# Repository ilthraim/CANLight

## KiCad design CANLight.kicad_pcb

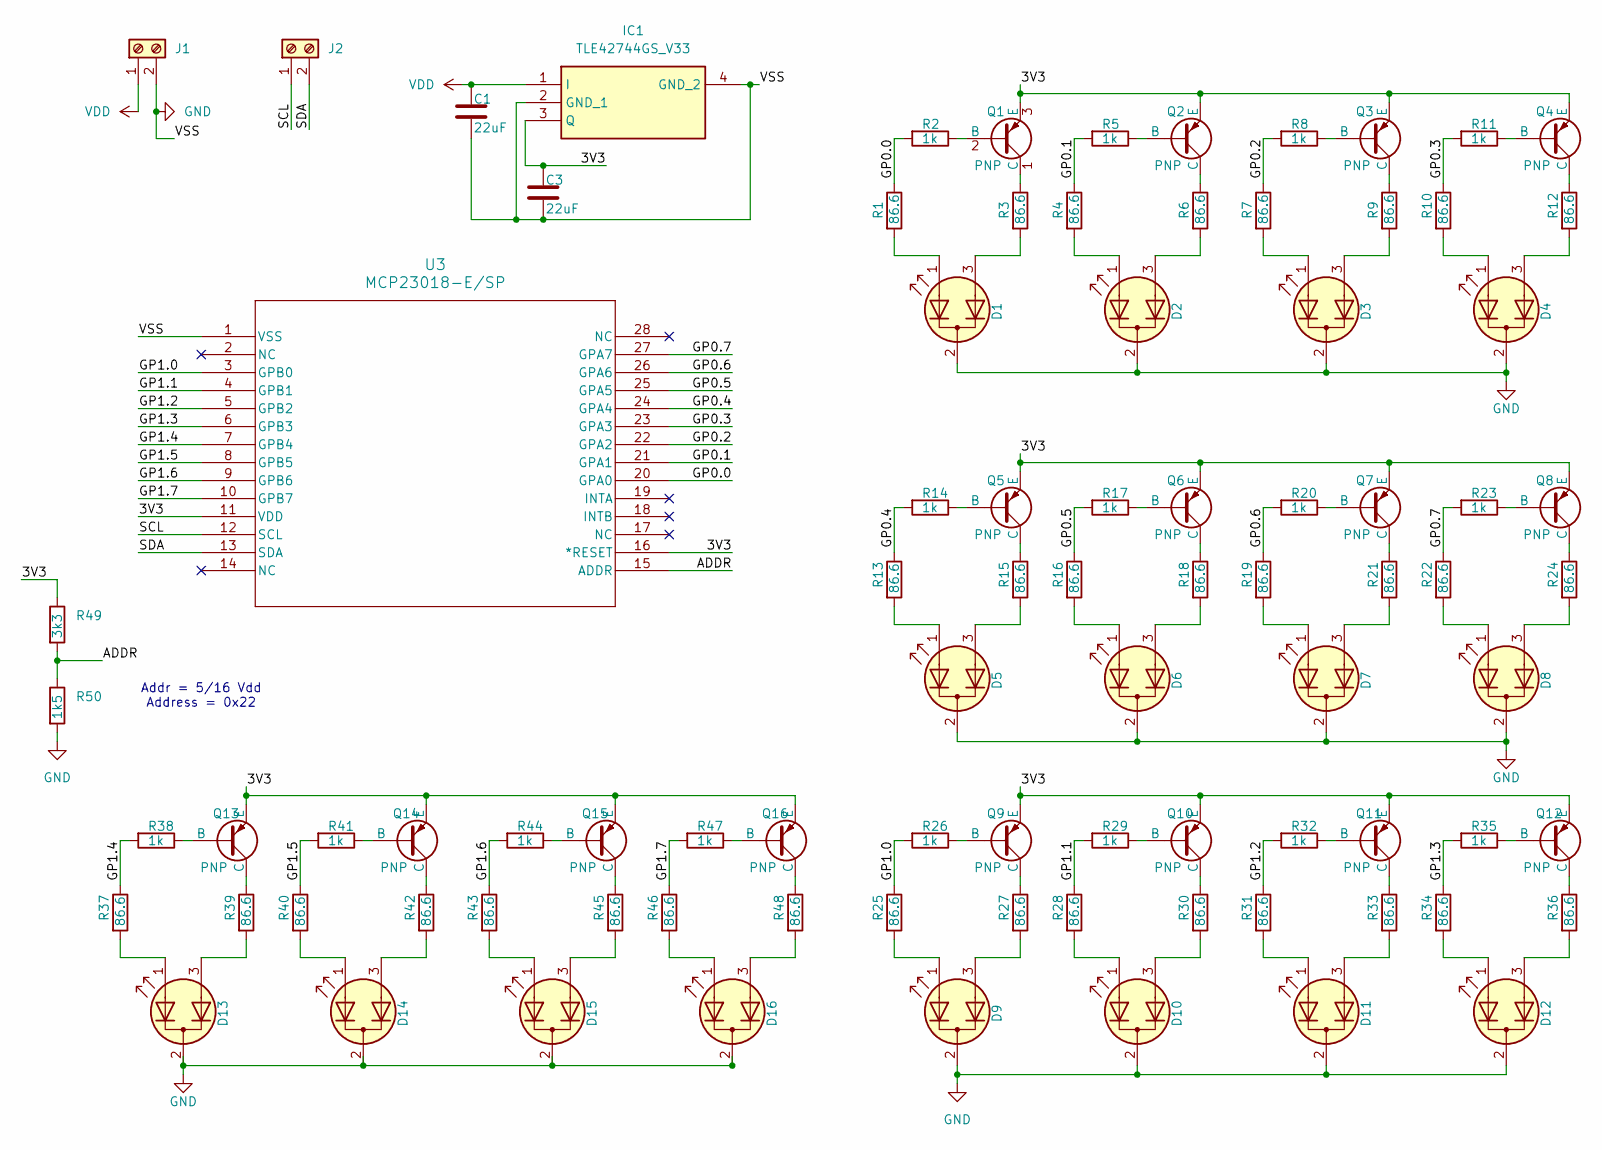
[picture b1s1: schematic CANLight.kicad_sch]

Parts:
C1, C3: 22uF; C_0805_2012Metric
D1, D2, D3, D4, D5, D6, D7, D8, D9, D10, D11, D12, D13, D14, D15, D16: LED_Dual_AKA; HLMP-40XX_BRA
IC1: TLE42744GS_V33; VREG_TLE42644GHTSA3; Mouser Part Number 726-TLE42744GSV33
J1, J2: Screw_Terminal_01x02; CONN_1935161_PXC
Q1, Q2, Q3, Q4, Q5, Q6, Q7, Q8, Q9, Q10, Q11, Q12, Q13, Q14, Q15, Q16: PNP; TO-92-3L_5P33X5P2_ONS
R1, R3, R4, R6, R7, R9, R10, R12, R13, R15, R16, R18, R19, R21, R22, R24, R25, R27, R28, R30, R31, R33, R34, R36, R37, R39, R40, R42, R43, R45, R46, R48: 86.6; R_0805_2012Metric
R2, R5, R8, R11, R14, R17, R20, R23, R26, R29, R32, R35, R38, R41, R44, R47: 1k; R_0805_2012Metric
R49: 3k3; R_0805_2012Metric
R50: 1k5; R_0805_2012Metric
U3: MCP23018-E/SP; SPDIP28_300MC_MCH

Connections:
/3V3: C3.1, IC1.3 (Q), Q1.3 (E), Q2.3 (E), Q3.3 (E), Q4.3 (E), Q5.3 (E), Q6.3 (E), Q7.3 (E), Q8.3 (E), Q9.3 (E), Q10.3 (E), Q11.3 (E), Q12.3 (E), Q13.3 (E), Q14.3 (E), Q15.3 (E), Q16.3 (E), R49.1, U3.11 (VDD), U3.16 (*RESET)
/ADDR: R49.2, R50.1, U3.15 (ADDR)
/GP0.0: R1.1, R2.2, U3.20 (GPA0)
/GP0.1: R4.1, R5.2, U3.21 (GPA1)
/GP0.2: R7.1, R8.2, U3.22 (GPA2)
/GP0.3: R10.1, R11.2, U3.23 (GPA3)
/GP0.4: R13.1, R14.2, U3.24 (GPA4)
/GP0.5: R16.1, R17.2, U3.25 (GPA5)
/GP0.6: R19.1, R20.2, U3.26 (GPA6)
/GP0.7: R22.1, R23.2, U3.27 (GPA7)
/GP1.0: R25.1, R26.2, U3.3 (GPB0)
/GP1.1: R28.1, R29.2, U3.4 (GPB1)
/GP1.2: R31.1, R32.2, U3.5 (GPB2)
/GP1.3: R34.1, R35.2, U3.6 (GPB3)
/GP1.4: R37.1, R38.2, U3.7 (GPB4)
/GP1.5: R40.1, R41.2, U3.8 (GPB5)
/GP1.6: R43.1, R44.2, U3.9 (GPB6)
/GP1.7: R46.1, R47.2, U3.10 (GPB7)
/SCL: J2.1, U3.12 (SCL)
/SDA: J2.2, U3.13 (SDA)
GND: C1.2, C3.2, D1.2 (K), D2.2 (K), D3.2 (K), D4.2 (K), D5.2 (K), D6.2 (K), D7.2 (K), D8.2 (K), D9.2 (K), D10.2 (K), D11.2 (K), D12.2 (K), D13.2 (K), D14.2 (K), D15.2 (K), D16.2 (K), IC1.2 (GND_1), IC1.4 (GND_2), J1.2, R50.2, U3.1 (VSS)
unnamed: D1.1 (A1), R1.2
unnamed: D1.3 (A2), R3.2
unnamed: D2.1 (A1), R4.2
unnamed: D2.3 (A2), R6.2
unnamed: D3.1 (A1), R7.2
unnamed: D3.3 (A2), R9.2
unnamed: D4.1 (A1), R10.2
unnamed: D4.3 (A2), R12.2
unnamed: D5.1 (A1), R13.2
unnamed: D5.3 (A2), R15.2
unnamed: D6.1 (A1), R16.2
unnamed: D6.3 (A2), R18.2
unnamed: D7.1 (A1), R19.2
unnamed: D7.3 (A2), R21.2
unnamed: D8.1 (A1), R22.2
unnamed: D8.3 (A2), R24.2
unnamed: D9.1 (A1), R25.2
unnamed: D9.3 (A2), R27.2
unnamed: D10.1 (A1), R28.2
unnamed: D10.3 (A2), R30.2
unnamed: D11.1 (A1), R31.2
unnamed: D11.3 (A2), R33.2
unnamed: D12.1 (A1), R34.2
unnamed: D12.3 (A2), R36.2
unnamed: D13.1 (A1), R37.2
unnamed: D13.3 (A2), R39.2
unnamed: D14.1 (A1), R40.2
unnamed: D14.3 (A2), R42.2
unnamed: D15.1 (A1), R43.2
unnamed: D15.3 (A2), R45.2
unnamed: D16.1 (A1), R46.2
unnamed: D16.3 (A2), R48.2
unnamed: Q1.2 (B), R2.1
unnamed: Q1.1 (C), R3.1
unnamed: Q2.2 (B), R5.1
unnamed: Q2.1 (C), R6.1
unnamed: Q3.2 (B), R8.1
unnamed: Q3.1 (C), R9.1
unnamed: Q4.2 (B), R11.1
unnamed: Q4.1 (C), R12.1
unnamed: Q5.2 (B), R14.1
unnamed: Q5.1 (C), R15.1
unnamed: Q6.2 (B), R17.1
unnamed: Q6.1 (C), R18.1
unnamed: Q7.2 (B), R20.1
unnamed: Q7.1 (C), R21.1
unnamed: Q8.2 (B), R23.1
unnamed: Q8.1 (C), R24.1
unnamed: Q9.2 (B), R26.1
unnamed: Q9.1 (C), R27.1
unnamed: Q10.2 (B), R29.1
unnamed: Q10.1 (C), R30.1
unnamed: Q11.2 (B), R32.1
unnamed: Q11.1 (C), R33.1
unnamed: Q12.2 (B), R35.1
unnamed: Q12.1 (C), R36.1
unnamed: Q13.2 (B), R38.1
unnamed: Q13.1 (C), R39.1
unnamed: Q14.2 (B), R41.1
unnamed: Q14.1 (C), R42.1
unnamed: Q15.2 (B), R44.1
unnamed: Q15.1 (C), R45.1
unnamed: Q16.2 (B), R47.1
unnamed: Q16.1 (C), R48.1
VDD: C1.1, IC1.1 (I), J1.1

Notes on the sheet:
Addr = 5/16 Vdd Address = 0x22

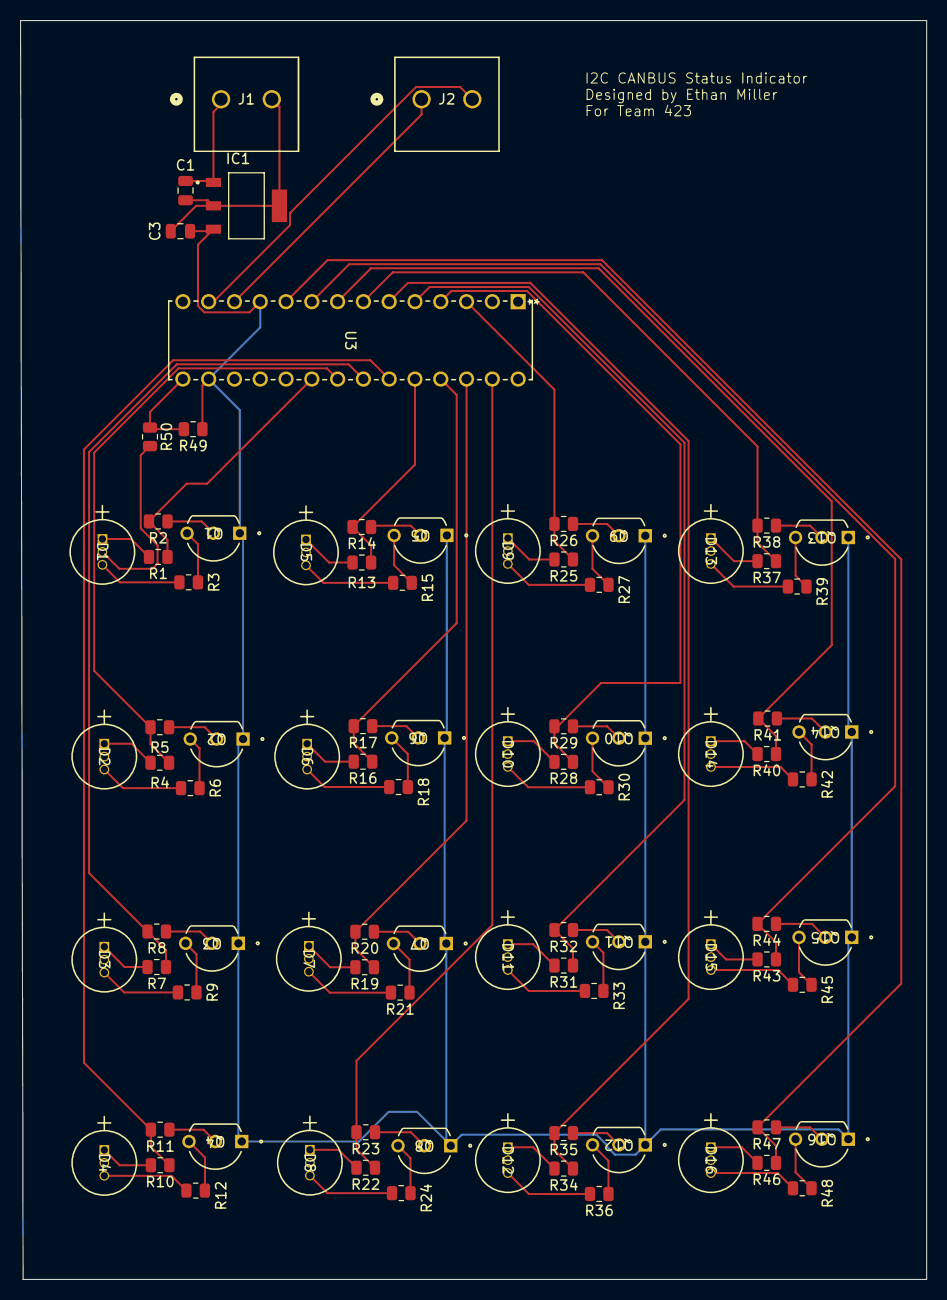
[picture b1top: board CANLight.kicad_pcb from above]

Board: 2 copper layers, 89.2 x 124.0 mm, 88 parts (0 on the bottom side), 86 nets.

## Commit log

2024-03-06 Initial PCB design
2024-03-06 Added Gerbers
